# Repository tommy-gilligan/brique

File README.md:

<p align="center">
  
  <h3 align="center">Brique</h3>
  <p align="center">
    An RP2354-based replacement mainboard for Nokia 3310.<br />
    Rust firmware with browser-based simulator included. 
    <br />
    <br />
    Software: <a href="https://tommy-gilligan.github.io/brique/simulation">Simulation</a>
    ·
    <a href="https://tommy-gilligan.github.io/brique/doc/shared">API</a>
    <br />
    Hardware: <a href="https://github.com/tommy-gilligan/brique/releases/latest/download/gerbers.zip">Gerbers</a>
    ·
    <a href="https://github.com/tommy-gilligan/brique/releases/latest/download/bom.csv">BOM</a>
    ·
    <a href="https://github.com/tommy-gilligan/brique/releases/latest/download/cpl.csv">CPL</a>
    ·
    <a href="https://github.com/tommy-gilligan/brique/releases/latest/download/schematic.pdf">Schematic</a>
    ·
    <a href="https://github.com/tommy-gilligan/brique/releases/latest/download/pcb.svg">PCB Layout</a>
  </p>
</p>
<hr/>
This started as a cute "what if?":

> What if I could type out messages on my smart phone by using tactile buttons like I used to have on my phone back in high school?

Because the board would need to fit into the chassis of a Nokia 3310 and because there are existing doodads that would be sitting alongside the board anyways, scope has crept to include connecting to these other thingamajigs.

## Assuming Rustup
```
curl --proto '=https' --tlsv1.2 -sSf https://sh.rustup.rs | sh
```
- select nightly
- load into shell

## Setting up web environment

```
cargo install --locked trunk
cd web
trunk serve
```

## Setting up rp environment

- Setting up board
    - Install Hardware Test Program
    - Reassemble 3310
    - Manual Test

## Ordering from JLCPCB
1.  Download the following files from [the latest release](https://github.com/tommy-gilligan/brique/releases/latest):
    - [gerbers.zip](https://github.com/tommy-gilligan/brique/releases/latest/download/gerbers.zip)
    - [bom.csv](https://github.com/tommy-gilligan/brique/releases/latest/download/bom.csv)
    - [cpl.csv](https://github.com/tommy-gilligan/brique/releases/latest/download/cpl.csv)
2. Upload `gerbers.zip`
3. Set `PCB Thickness` to `1.0mm`.  This is the thickness of the original board that is being replaced.  The case is not designed for boards that are not 1mm thick.
4. Enable `PCB Assembly`
5. Set `Assembly Side` to `Bottom Side`
6. Set `PCBA Qty` to `2` (or however many you like, but 2 is the minimum)
7. Click `Next` to be taken to the next page
8. Upload `bom.csv`
9. Upload `cpl.csv`
10. Click `Process BOM & CPL`

### TODO

- document app API

- give more control over display flushing, keep track of what needs updating, what needs flushing
	- display can do 90deg rotated addressing
- allow setting time
- rp2350 very low power state
- make all system work live on primary core.  give apps dedicated secondary core.
- 'pre-emption'
- priveledged, background blocking system calls  
- defmt should be used if possible (instead of log).  currently it is used for uart/rtt but for usb i'm using log.  is there a way to use usb logging from defmt?  will probably require a bit of a bit deep dive
- placement of some parts is off (rotation for U*)
- switch off after 5 minutes idle (switching on takes no time)
- power button: can this be triggered by 'any key'?  ie. any keypad press turns the device on.  there's enough GPIO to spare that we should have a dedicated GPIO for any key too)
- power button should turn on device but also function as gpio?

https://serdisplib.sourceforge.net/ser/pcd8544.html

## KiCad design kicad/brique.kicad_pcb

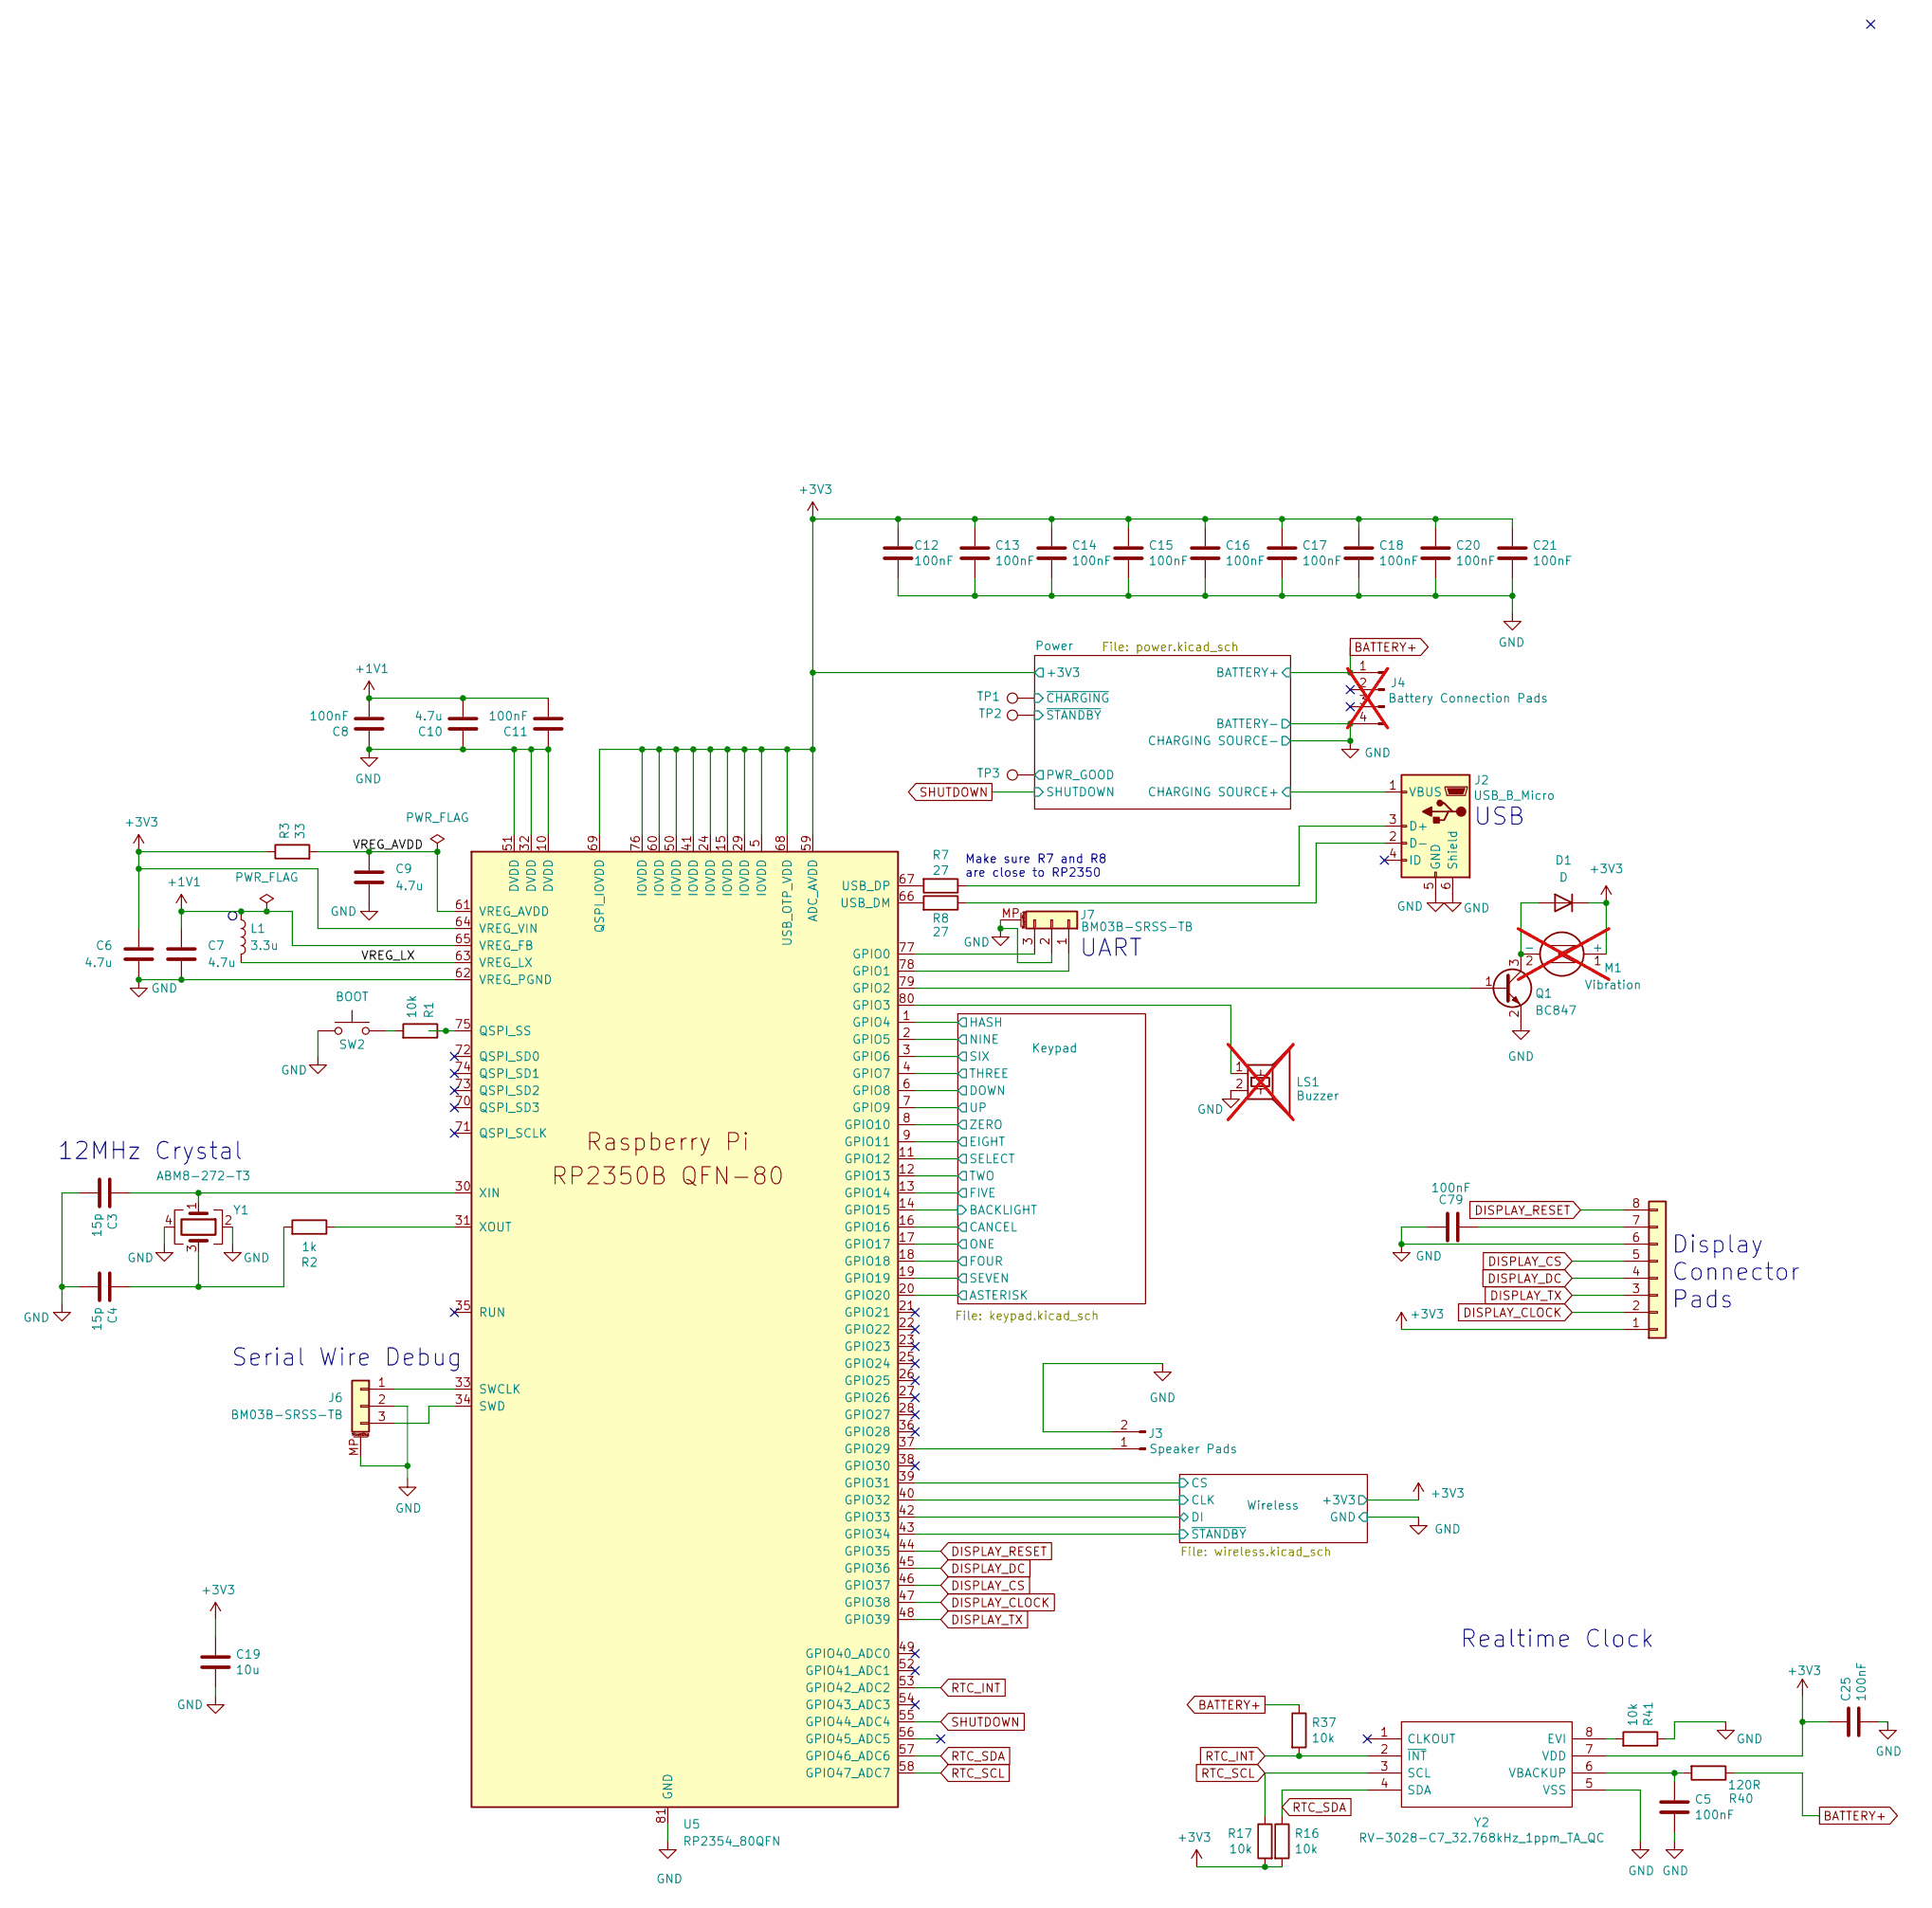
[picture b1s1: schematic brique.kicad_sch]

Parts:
C3, C4: 15p; C_0402_1005Metric; JLCPCB C86285
C5, C8, C11, C12, C13, C14, C15, C16, C17, C18, C20, C21, C79: 100nF; C_0402_1005Metric; JLCPCB C1525
C6, C7, C9, C10: 4.7u; C_0402_1005Metric; JLCPCB C368809
C19: 10u; C_0805_2012Metric; JLCPCB C17024
C25: 100nF; C_0805_2012Metric; JLCPCB C49678
D1: D; D_0402_1005Metric; JLCPCB C2837790
J1: Conn_01x07; screen
J2: USB_B_Micro; USB_Micro-B_Molex_47346-0001; JLCPCB C132560
J3: Speaker Pads; PinHeader_1x02_P1.00mm_Vertical_SMD_Pin1Left
J4: Battery Connection Pads; battery; not fitted
J6, J7: BM03B-SRSS-TB; JST_SH_SM03B-SRSS-TB_1x03-1MP_P1.00mm_Horizontal; JLCPCB C160389
L1: 3.3u; L_pol_2016; JLCPCB C42411119
LS1: Buzzer; buzzer; not fitted
M1: Vibration; vibrator; not fitted
Q1: BC847; SOT-23; JLCPCB C391423
R1, R16, R17, R37, R41: 10k; R_0402_1005Metric; JLCPCB C60490
R2: 1k; R_0402_1005Metric; JLCPCB C25543
R3: 33; R_0402_1005Metric; JLCPCB C852729
R7, R8: 27; R_0402_1005Metric; JLCPCB C25100
R40: 120R; R_0402_1005Metric; JLCPCB C114758
SW2: BOOT; SW_SPST_PTS810; JLCPCB C221895
TP1, TP2, TP3: TestPoint; TestPoint_THTPad_D1.5mm_Drill0.7mm
U5: RP2354_80QFN; RP2350-QFN-80-1EP_10x10_P0.4mm_EP3.4x3.4mm_ThermalVias; JLCPCB C39843328
Y1: ABM8-272-T3; Crystal_SMD_3225-4Pin_3.2x2.5mm; JLCPCB C20625731
Y2: RV-3028-C7_32.768kHz_1ppm_TA_QC; MicroCrystal_RV3028C7; Mouser Part Number 428-203591-MG01

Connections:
+1V1: C7.1, C8.2, C10.2, C11.2, L1.1, U5.65 (VREG_FB)
+3V3: C6.1, C12.1, C13.1, C14.1, C15.1, C16.1, C17.1, C18.1, C19.1, C20.1, C21.1, C25.1, D1.1 (K), J1.1, M1.1 (+), R3.1, R16.2, R17.2, U5.5 (IOVDD), U5.15 (IOVDD), U5.24 (IOVDD), U5.29 (IOVDD), U5.41 (IOVDD), U5.50 (IOVDD), U5.59 (ADC_AVDD), U5.60 (IOVDD), U5.64 (VREG_VIN), U5.68 (USB_OTP_VDD), U5.69 (QSPI_IOVDD), U5.76 (IOVDD), Y2.7 (VDD); also elsewhere on the board
/Keypad/ASTERISK: U5.20 (GPIO20); also elsewhere on the board
/Keypad/BACKLIGHT: U5.14 (GPIO15); also elsewhere on the board
/Keypad/CANCEL: U5.16 (GPIO16); also elsewhere on the board
/Keypad/DOWN: U5.6 (GPIO8); also elsewhere on the board
/Keypad/EIGHT: U5.9 (GPIO11); also elsewhere on the board
/Keypad/FIVE: U5.13 (GPIO14); also elsewhere on the board
/Keypad/FOUR: U5.18 (GPIO18); also elsewhere on the board
/Keypad/HASH: U5.1 (GPIO4); also elsewhere on the board
/Keypad/NINE: U5.2 (GPIO5); also elsewhere on the board
/Keypad/ONE: U5.17 (GPIO17); also elsewhere on the board
/Keypad/SELECT: U5.11 (GPIO12); also elsewhere on the board
/Keypad/SEVEN: U5.19 (GPIO19); also elsewhere on the board
/Keypad/SIX: U5.3 (GPIO6); also elsewhere on the board
/Keypad/THREE: U5.4 (GPIO7); also elsewhere on the board
/Keypad/TWO: U5.12 (GPIO13); also elsewhere on the board
/Keypad/UP: U5.7 (GPIO9); also elsewhere on the board
/Keypad/ZERO: U5.8 (GPIO10); also elsewhere on the board
/Power/CHARGING SOURCE+: J2.1 (VBUS); also elsewhere on the board
/Power/PWR_GOOD: TP3.1; also elsewhere on the board
/Power/~CHARGING: TP1.1; also elsewhere on the board
/Power/~STANDBY: TP2.1; also elsewhere on the board
/VREG_AVDD: C9.1, R3.2, U5.61 (VREG_AVDD)
/VREG_LX: L1.2, U5.63 (VREG_LX)
/Wireless/CLK: U5.40 (GPIO32); also elsewhere on the board
/Wireless/CS: U5.39 (GPIO31); also elsewhere on the board
/Wireless/DI: U5.42 (GPIO33); also elsewhere on the board
/Wireless/~STANDBY: U5.43 (GPIO34); also elsewhere on the board
BATTERY+: J4.1, R37.1, R40.1; also elsewhere on the board
DISPLAY_CLOCK: J1.2, U5.47 (GPIO38)
DISPLAY_CS: J1.5, U5.46 (GPIO37)
DISPLAY_DC: J1.4, U5.45 (GPIO36)
DISPLAY_RESET: J1.8, U5.44 (GPIO35)
DISPLAY_TX: J1.3, U5.48 (GPIO39)
GND: C3.2, C4.2, C5.2, C6.2, C7.2, C8.1, C9.2, C10.1, C11.1, C12.2, C13.2, C14.2, C15.2, C16.2, C17.2, C18.2, C19.2, C20.2, C21.2, C25.2, C79.1, J1.6, J2.5 (GND), J2.6 (Shield), J3.2, J4.4, J6.2, J6.MP (MountPin), J7.2, J7.MP (MountPin), LS1.2, Q1.2 (E), R41.1, SW2.1, U5.10 (DVDD), U5.32 (DVDD), U5.51 (DVDD), U5.62 (VREG_PGND), U5.81 (GND), Y1.2, Y1.4, Y2.5 (VSS); also elsewhere on the board
unnamed: C4.1, R2.2, Y1.3
unnamed: D1.2 (A), M1.2 (-), Q1.3 (C)
unnamed: C79.2, J1.7
unnamed: J2.3 (D+), R7.1
unnamed: J2.2 (D-), R8.1
unnamed: J3.1, U5.37 (GPIO29)
unnamed: J6.1, U5.33 (SWCLK)
unnamed: J6.3, U5.34 (SWD)
unnamed: J7.1, U5.78 (GPIO1)
unnamed: J7.3, U5.77 (GPIO0)
unnamed: Q1.1 (B), U5.79 (GPIO2)
unnamed: R1.2, SW2.2
unnamed: LS1.1, U5.80 (GPIO3)
unnamed: R1.1, U5.75 (QSPI_SS)
unnamed: R8.2, U5.66 (USB_DM)
unnamed: R7.2, U5.67 (USB_DP)
unnamed: C3.1, U5.30 (XIN), Y1.1
unnamed: R2.1, U5.31 (XOUT)
unnamed: R41.2, Y2.8 (EVI)
unnamed: C5.1, R40.2, Y2.6 (VBACKUP)
RTC_INT: R37.2, U5.53 (GPIO42_ADC2), Y2.2 (~INT)
RTC_SCL: R17.1, U5.58 (GPIO47_ADC7), Y2.3 (SCL)
RTC_SDA: R16.1, U5.57 (GPIO46_ADC6), Y2.4 (SDA)
SHUTDOWN: U5.55 (GPIO44_ADC4); also elsewhere on the board

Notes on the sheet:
Make sure R7 and R8 are close to RP2350
Serial Wire Debug
Realtime Clock
Display Connector Pads
USB
UART
12MHz Crystal

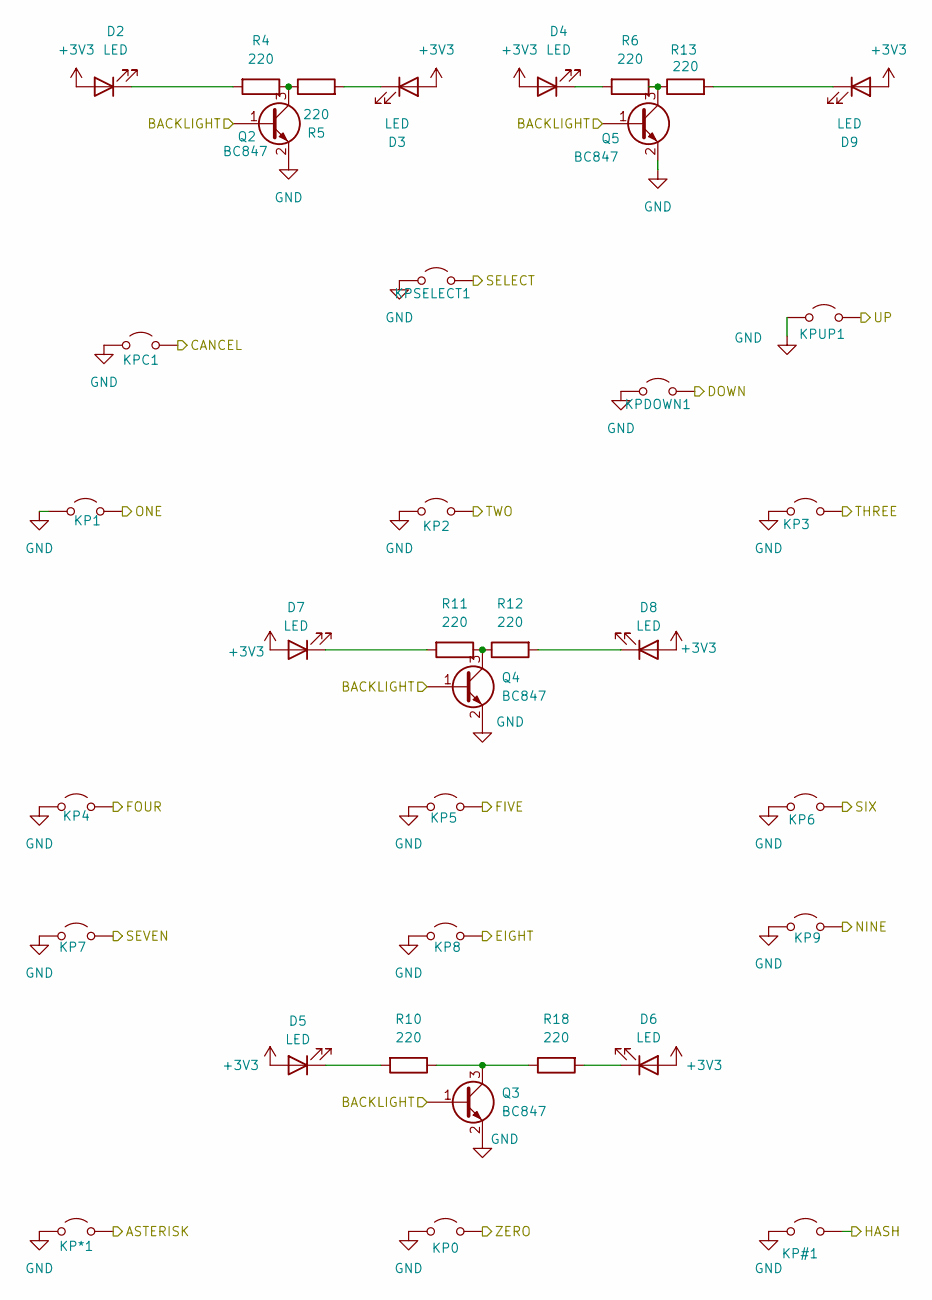
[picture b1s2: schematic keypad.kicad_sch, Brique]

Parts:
D2, D3, D4, D5, D6, D7, D8, D9: LED; LED_REVERSE; JLCPCB C3646932
KP0, KP1, KP2, KP4, KP5, KP6, KP7, KP8, KP9: Jumper_2_Open; ButtonPads
KP3: 3; ButtonPads
KP#1: Jumper_2_Open; ButtonPads
KP*1: Jumper_2_Open; ButtonPads
KPC1: C; ButtonPads
KPDOWN1: Jumper_2_Open; ButtonPads
KPSELECT1: Jumper_2_Open; ButtonPads
KPUP1: Jumper_2_Open; ButtonPads
Q2, Q3, Q4, Q5: BC847; SOT-23; JLCPCB C391423
R4, R5, R6, R10, R11, R12, R13, R18: 220; R_0402_1005Metric; JLCPCB C112291

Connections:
+3V3: D2.2 (A), D3.2 (A), D4.2 (A), D5.2 (A), D6.2 (A), D7.2 (A), D8.2 (A), D9.2 (A); also elsewhere on the board
/Keypad/ASTERISK: KP*1.2 (B); also elsewhere on the board
/Keypad/BACKLIGHT: Q2.1 (B), Q3.1 (B), Q4.1 (B), Q5.1 (B); also elsewhere on the board
/Keypad/CANCEL: KPC1.2 (B); also elsewhere on the board
/Keypad/DOWN: KPDOWN1.2 (B); also elsewhere on the board
/Keypad/EIGHT: KP8.2 (B); also elsewhere on the board
/Keypad/FIVE: KP5.2 (B); also elsewhere on the board
/Keypad/FOUR: KP4.2 (B); also elsewhere on the board
/Keypad/HASH: KP#1.2 (B); also elsewhere on the board
/Keypad/NINE: KP9.2 (B); also elsewhere on the board
/Keypad/ONE: KP1.2 (B); also elsewhere on the board
/Keypad/SELECT: KPSELECT1.2 (B); also elsewhere on the board
/Keypad/SEVEN: KP7.2 (B); also elsewhere on the board
/Keypad/SIX: KP6.2 (B); also elsewhere on the board
/Keypad/THREE: KP3.2 (B); also elsewhere on the board
/Keypad/TWO: KP2.2 (B); also elsewhere on the board
/Keypad/UP: KPUP1.2 (B); also elsewhere on the board
/Keypad/ZERO: KP0.2 (B); also elsewhere on the board
GND: KP0.1 (A), KP1.1 (A), KP2.1 (A), KP3.1 (A), KP4.1 (A), KP5.1 (A), KP6.1 (A), KP7.1 (A), KP8.1 (A), KP9.1 (A), KP#1.1 (A), KP*1.1 (A), KPC1.1 (A), KPDOWN1.1 (A), KPSELECT1.1 (A), KPUP1.1 (A), Q2.2 (E), Q3.2 (E), Q4.2 (E), Q5.2 (E); also elsewhere on the board
unnamed: D2.1 (K), R4.2
unnamed: D3.1 (K), R5.2
unnamed: D4.1 (K), R6.2
unnamed: D5.1 (K), R10.2
unnamed: D6.1 (K), R18.2
unnamed: D7.1 (K), R11.2
unnamed: D8.1 (K), R12.2
unnamed: D9.1 (K), R13.2
unnamed: Q2.3 (C), R4.1, R5.1
unnamed: Q3.3 (C), R10.1, R18.1
unnamed: Q4.3 (C), R11.1, R12.1
unnamed: Q5.3 (C), R6.1, R13.1

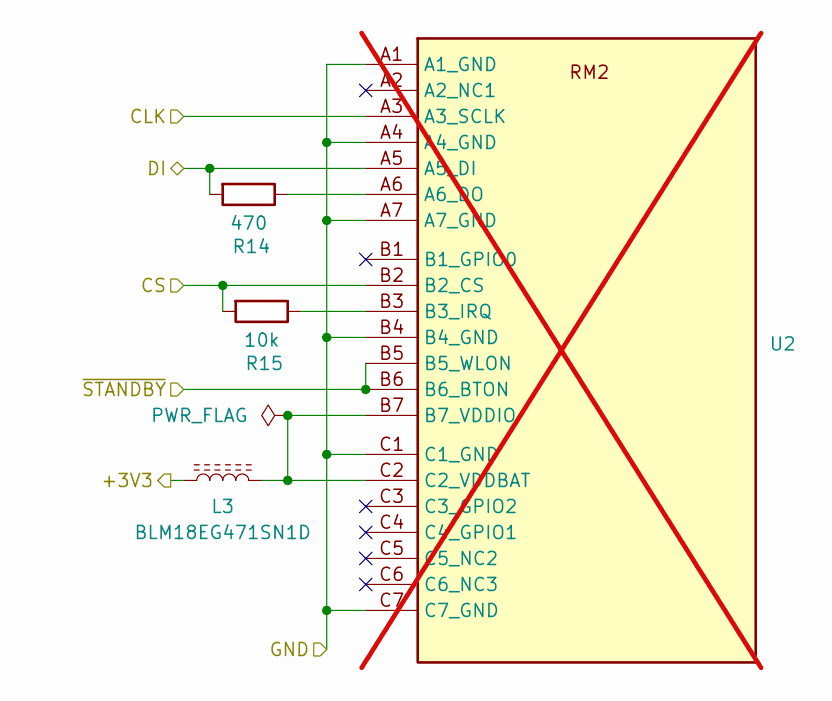
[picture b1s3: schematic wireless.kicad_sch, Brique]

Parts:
L3: BLM18EG471SN1D; L_0201_0603Metric; JLCPCB C337880
R14: 470; R_0402_1005Metric; JLCPCB C114877
R15: 10k; R_0402_1005Metric; JLCPCB C60490
U2: RM2; not fitted

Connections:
+3V3: L3.1; also elsewhere on the board
/Wireless/CLK: U2.A3 (A3_SCLK); also elsewhere on the board
/Wireless/CS: R15.2, U2.B2 (B2_CS); also elsewhere on the board
/Wireless/DI: R14.2, U2.A5 (A5_DI); also elsewhere on the board
/Wireless/~STANDBY: U2.B5 (B5_WLON), U2.B6 (B6_BTON); also elsewhere on the board
GND: U2.A1 (A1_GND), U2.A4 (A4_GND), U2.A7 (A7_GND), U2.B4 (B4_GND), U2.C1 (C1_GND), U2.C7 (C7_GND); also elsewhere on the board
unnamed: R14.1, U2.A6 (A6_DO)
unnamed: R15.1, U2.B3 (B3_IRQ)
unnamed: L3.2, U2.B7 (B7_VDDIO), U2.C2 (C2_VDDBAT)

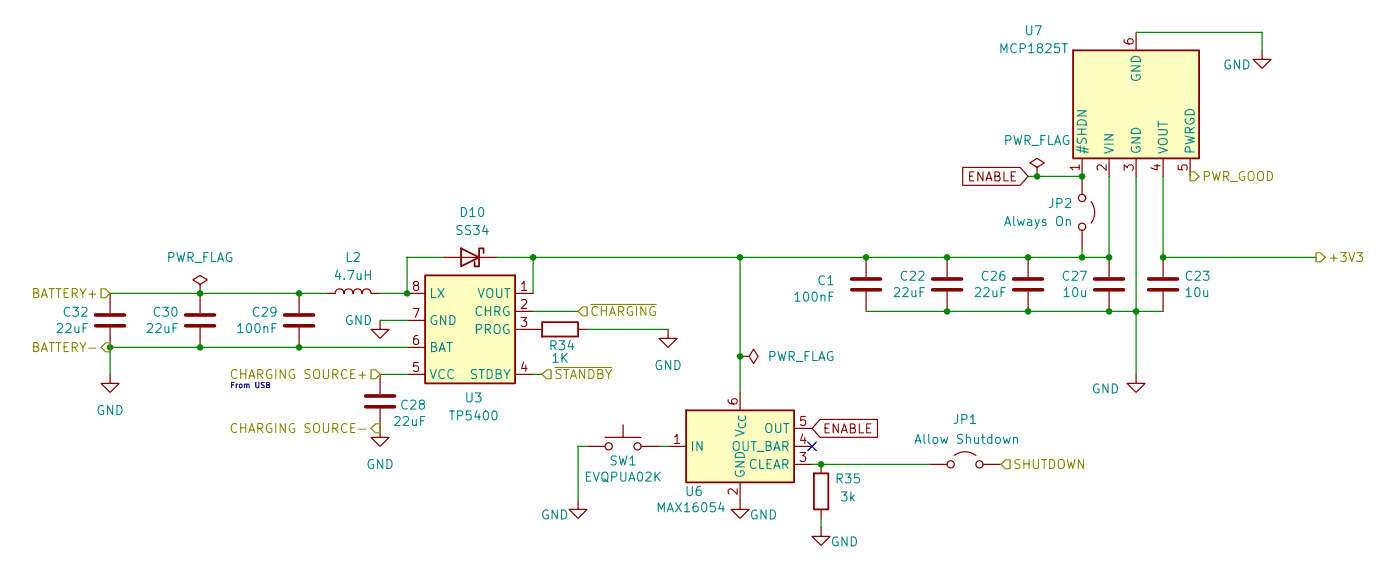
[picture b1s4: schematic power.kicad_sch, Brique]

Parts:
C1, C29: 100nF; C_0805_2012Metric; JLCPCB C49678
C22, C26, C28, C30, C32: 22uF; C_0805_2012Metric; JLCPCB C602037
C23, C27: 10u; C_0805_2012Metric; JLCPCB C17024
D10: SS34; D_SMA; JLCPCB C8678
JP1: Allow Shutdown; SolderJumper-2_P1.3mm_Open_Pad1.0x1.5mm
JP2: Always On; SolderJumper-2_P1.3mm_Open_Pad1.0x1.5mm
L2: 4.7uH; L_Neosid_MicroCoil_Ms36-L; JLCPCB C57269
R34: 1K; R_0402_1005Metric; JLCPCB C25543
R35: 3k; R_0402_1005Metric; JLCPCB C137872
SW1: EVQPUA02K; power switch; JLCPCB C128539
U3: TP5400; SOIC-8_3.9x4.9mm_P1.27mm; JLCPCB C2891434
U6: MAX16054; SOT-23-6; JLCPCB C79401
U7: MCP1825T; SOT-223-6; JLCPCB C622691

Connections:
+3V3: C23.1, U7.4 (VOUT); also elsewhere on the board
/Power/CHARGING SOURCE+: C28.1, U3.5 (VCC); also elsewhere on the board
/Power/PWR_GOOD: U7.5 (PWRGD); also elsewhere on the board
/Power/~CHARGING: U3.2 (CHRG); also elsewhere on the board
/Power/~STANDBY: U3.4 (STDBY); also elsewhere on the board
BATTERY+: C29.1, C30.1, C32.1, L2.2; also elsewhere on the board
ENABLE: JP2.2 (B), U6.5 (OUT), U7.1 (#SHDN)
GND: C1.2, C22.2, C23.2, C26.2, C27.2, C28.2, C29.2, C30.2, C32.2, R34.1, R35.1, SW1.1, U3.6 (BAT), U3.7 (GND), U6.2 (GND), U7.3 (GND), U7.6 (GND); also elsewhere on the board
unnamed: D10.2 (A), L2.1, U3.8 (LX)
unnamed: C1.1, C22.1, C26.1, C27.1, D10.1 (K), JP2.1 (A), U3.1 (VOUT), U6.6 (V_{CC}), U7.2 (VIN)
unnamed: JP1.1 (A), R35.2, U6.3 (CLEAR)
unnamed: R34.2, U3.3 (PROG)
unnamed: SW1.2, U6.1 (IN)
SHUTDOWN: JP1.2 (B); also elsewhere on the board

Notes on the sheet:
From USB

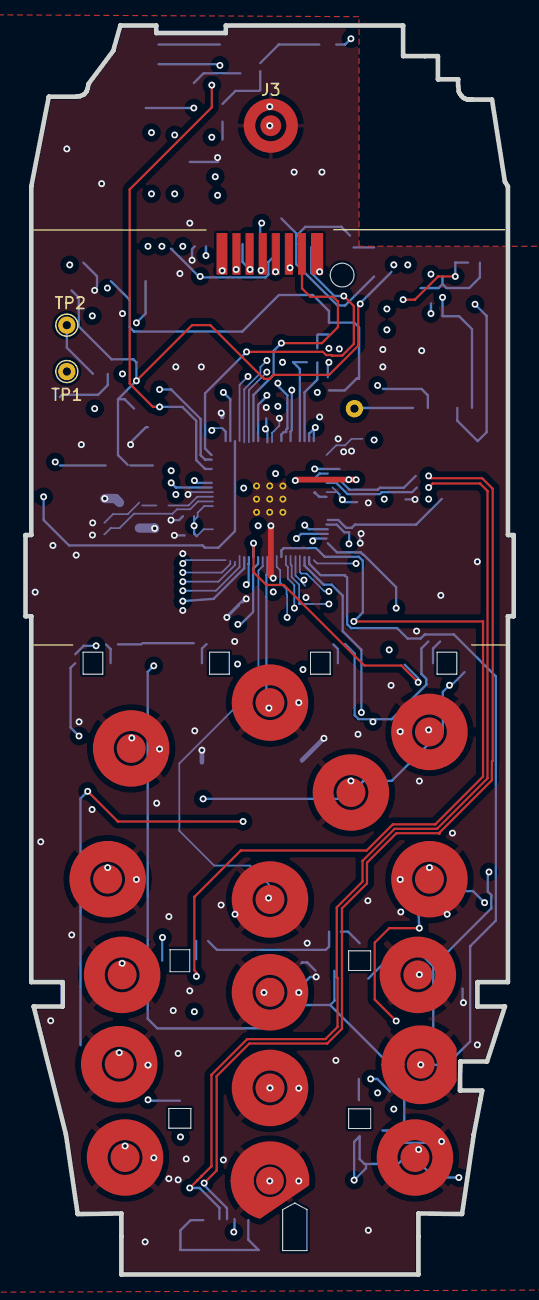
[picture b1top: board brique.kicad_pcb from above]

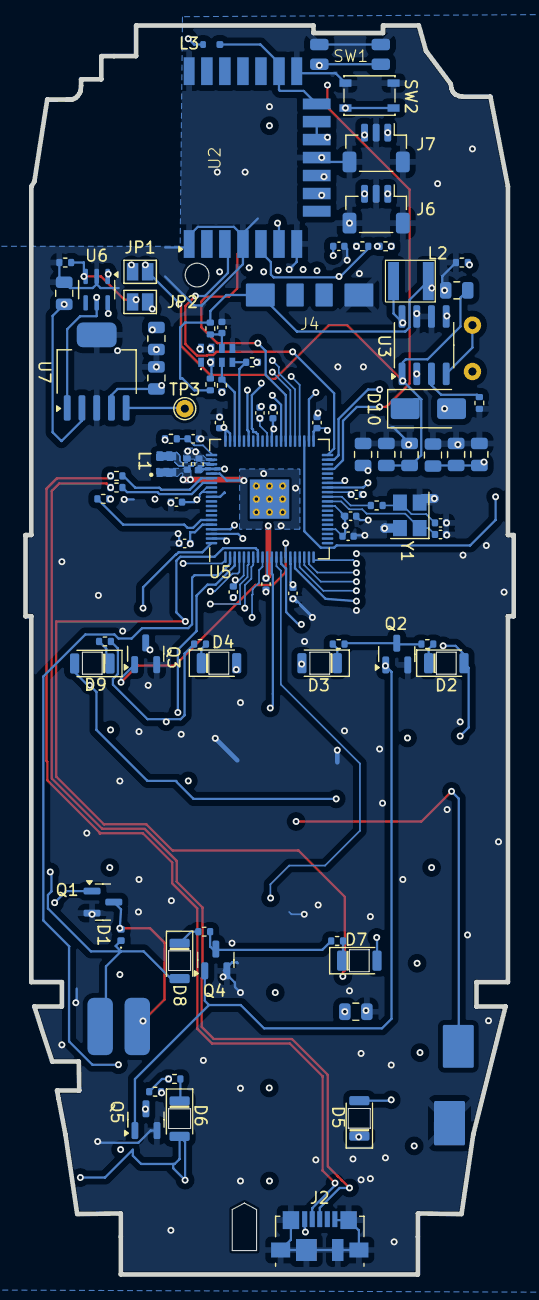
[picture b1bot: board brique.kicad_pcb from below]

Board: 4 copper layers, 42.1 x 107.7 mm, 108 parts (88 on the bottom side), 81 nets.

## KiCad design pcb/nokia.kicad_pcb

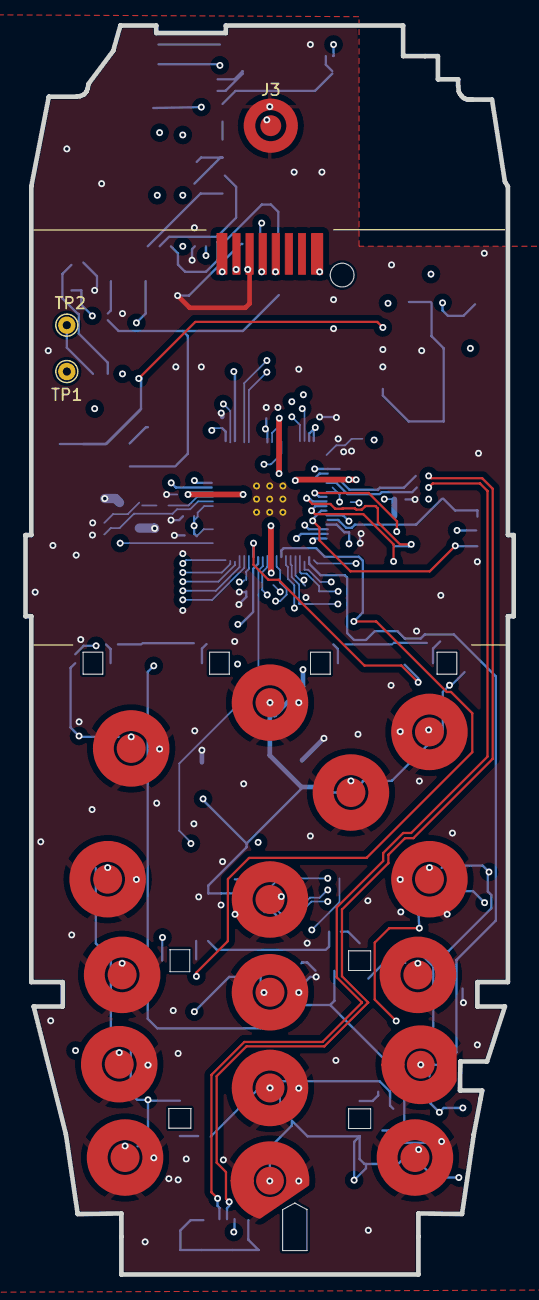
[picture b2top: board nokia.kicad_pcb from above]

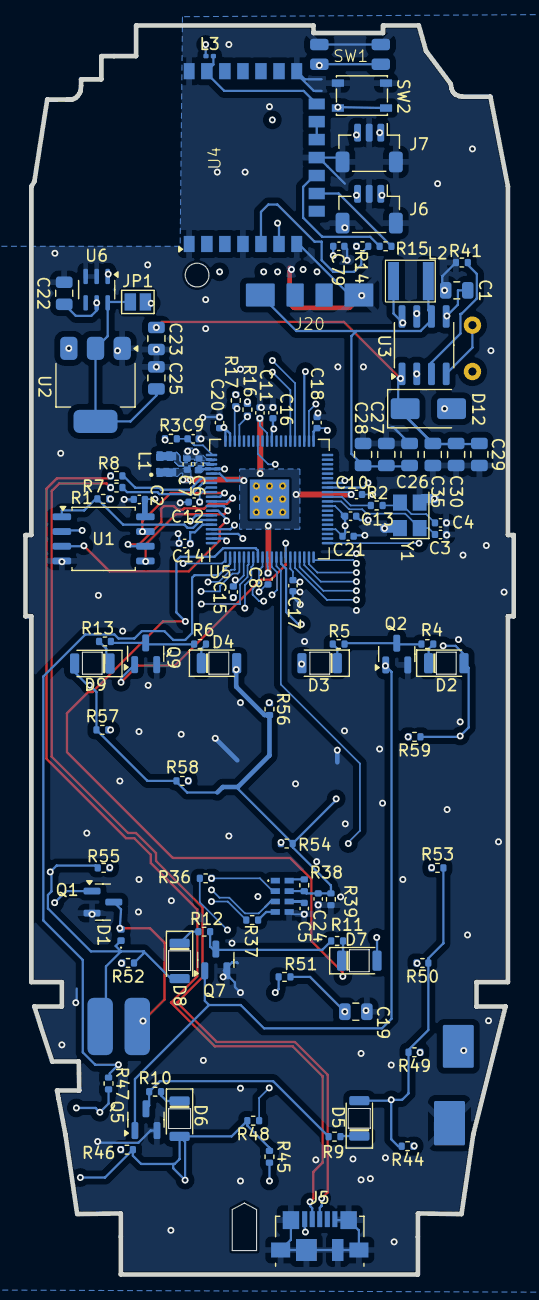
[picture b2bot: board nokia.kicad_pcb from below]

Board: 4 copper layers, 42.1 x 107.7 mm, 125 parts (105 on the bottom side), 81 nets.

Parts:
C1, C27, C28, C30, C35: 22uF; C_0805_2012Metric
C2, C5, C8, C11, C12, C13, C14, C15, C16, C17, C18, C20, C21, C24: 100n; C_0402_1005Metric
C3, C4: 15p; C_0402_1005Metric
C6, C7, C9, C10: 4.7u; C_0402_1005Metric
C19, C22, C23, C25: 10u; C_0805_2012Metric
C26, C29: 100nF; C_0805_2012Metric
C79: 100nF; C_0402_1005Metric
D1: D; D_0402_1005Metric
D2, D3, D4, D5, D6, D7, D8, D9: LED; LED_REVERSE
D12: SS34; D_SMA
J1: Conn_01x07; screen
J3: Conn_01x02_Pin; PinHeader_1x02_P1.00mm_Vertical_SMD_Pin1Left
J5: USB_B_Micro; USB_Micro-B_Molex_47346-0001
J6, J7: SM03B-SRSS-TB; JST_SH_BM03B-SRSS-TB_1x03-1MP_P1.00mm_Vertical
J20: Battery Connection Pads; battery
JP1: Jumper_2_Open; SolderJumper-2_P1.3mm_Open_Pad1.0x1.5mm
KP0, KP1, KP2, KP4, KP5, KP6, KP7, KP8, KP9: Jumper_2_Open; thick-pad
KP3: 3; thick-pad
KP#1: Jumper_2_Open; thick-pad
KP*1: Jumper_2_Open; thick-pad
KPC1: C; thick-pad
KPDOWN1: Jumper_2_Open; thick-pad
KPSELECT1: Jumper_2_Open; thick-pad
KPUP1: Jumper_2_Open; thick-pad
L1: 3.3u; L_pol_2016
L2: 4.7uH; L_Neosid_MicroCoil_Ms36-L
L3: BLM18EG471SN1D; L_0201_0603Metric
LS2: Buzzer; buzzer
M1: Vibration; vibrator
Q1, Q2, Q5, Q7, Q9: BC847; SOT-23
R1, R15, R16, R17, R36, R38: 10k; R_0402_1005Metric
R2: 1k; R_0402_1005Metric
R3: 33; R_0402_1005Metric
R4, R5, R6, R9, R10, R11, R12, R13: 220; R_0402_1005Metric
R7, R8: 27; R_0402_1005Metric
R14: 470; R_0402_1005Metric
R37: 120R; R_0402_1005Metric
R39: 100k; R_0402_1005Metric
R41: 1K; R_0402_1005Metric
R44, R45, R46, R47, R48, R49, R50, R51, R52, R53, R54, R55, R56, R57, R58, R59: 3k; R_0402_1005Metric
SW1: SW_Push; power switch
SW2: SW_Push; SW_SPST_PTS810
TP1, TP2: TestPoint; TestPoint_THTPad_D1.5mm_Drill0.7mm
U1: W25Q128JVS; SOIC-8_5.23x5.23mm_P1.27mm
U2: NCP1117-3.3_SOT223; SOT-223-3_TabPin2
U3: TP5400; SOIC-8_3.9x4.9mm_P1.27mm
U4: RM2
U5: RP2350_80QFN; RP2350-QFN-80-1EP_10x10_P0.4mm_EP3.4x3.4mm_ThermalVias
U6: MAX16054; SOT-23-6
Y1: ABM8-272-T3; Crystal_SMD_3225-4Pin_3.2x2.5mm
Y2: RV-3028-C7_32.768kHz_1ppm_TA_QC; MicroCrystal_RV3028C7

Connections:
+1V1: C7.1, C8.1, C10.1, C11.1, L1.1, U5.10 (DVDD), U5.32 (DVDD), U5.51 (DVDD), U5.65 (VREG_FB)
+3V3: C2.1, C6.1, C12.1, C13.1, C14.1, C15.1, C16.1, C17.1, C18.1, C19.1, C20.1, C21.1, C22.1, C24.1, D1.1 (K), D2.2 (A), D3.2 (A), D4.2 (A), D5.2 (A), D6.2 (A), D7.2 (A), D8.2 (A), D9.2 (A), J1.1, JP1.2 (B), L3.1, M1.1 (+), R3.1, R16.2, R17.1, R36.1, R38.1, R39.1, R44.2, R45.2, R46.2, R47.2, R48.2, R49.2, R50.1, R51.1, R52.1, R53.2, R54.2, R55.1, R56.2, R57.1, R58.1, R59.1, U1.8 (VCC), U5.5 (IOVDD), U5.15 (IOVDD), U5.24 (IOVDD), U5.29 (IOVDD), U5.41 (IOVDD), U5.50 (IOVDD), U5.59 (ADC_AVDD), U5.60 (IOVDD), U5.64 (VREG_VIN), U5.68 (USB_OTP_VDD), U5.69 (QSPI_IOVDD), U5.76 (IOVDD), U6.5 (OUT), Y2.7 (VDD)
+5V: C23.1, C29.2, C30.2, C35.2, D12.1 (K), U2.3 (VI), U3.1 (VOUT)
+BATT: C26.1, C27.1, C28.1, J20.1, L2.2, U3.6 (BAT)
-BATT: C1.2, C2.2, C3.2, C4.2, C5.2, C6.2, C7.2, C8.2, C9.2, C10.2, C11.2, C12.2, C13.2, C14.2, C15.2, C16.2, C17.2, C18.2, C19.2, C20.2, C21.2, C22.2, C23.2, C24.2, C25.2, C26.2, C27.2, C28.2, C29.1, C30.1, C35.1, C79.1, J1.6, J3.2, J5.5 (GND), J5.6 (Shield), J6.2, J6.MP (MountPin), J7.2, J7.MP (MountPin), J20.4, KP0.1 (A), KP1.1 (A), KP2.1 (A), KP3.1 (A), KP4.1 (A), KP5.1 (A), KP6.1 (A), KP7.1 (A), KP8.1 (A), KP9.1 (A), KP#1.1 (A), KP*1.1 (A), KPC1.1 (A), KPDOWN1.1 (A), KPSELECT1.1 (A), KPUP1.1 (A), LS2.2, Q1.2 (E), Q2.2 (E), Q5.2 (E), Q7.2 (E), Q9.2 (E), R39.2, R41.1, SW1.1, SW2.1, U1.4 (GND), U2.1 (GND), U3.7 (GND), U4.A1 (A1_GND), U4.A4 (A4_GND), U4.A7 (A7_GND), U4.B4 (B4_GND), U4.C1 (C1_GND), U4.C7 (C7_GND), U5.62 (VREG_PGND), U5.81 (GND), U6.2 (GND), U6.3 (CLEAR), Y1.2, Y1.4, Y2.5 (VSS)
/VREG_AVDD: C9.1, R3.2, U5.61 (VREG_AVDD)
/VREG_LX: L1.2, U5.63 (VREG_LX)
EVI: R38.2, Y2.8 (EVI)
GPIO0: J7.3, U5.77 (GPIO0)
GPIO1: J7.1, U5.78 (GPIO1)
GPIO2: Q1.1 (B), U5.79 (GPIO2)
GPIO4: KP#1.2 (B), R46.1, U5.1 (GPIO4)
GPIO5: KP9.2 (B), R47.1, U5.2 (GPIO5)
GPIO6: KP6.2 (B), R52.2, U5.3 (GPIO6)
GPIO7: KP3.2 (B), R55.2, U5.4 (GPIO7)
GPIO8: KPDOWN1.2 (B), R58.2, U5.6 (GPIO8)
GPIO9: KPUP1.2 (B), R57.2, U5.7 (GPIO9)
GPIO10: KP0.2 (B), R45.1, U5.8 (GPIO10)
GPIO11: KP8.2 (B), R48.1, U5.9 (GPIO11)
GPIO12: KPSELECT1.2 (B), R56.1, U5.11 (GPIO12)
GPIO13: KP2.2 (B), R54.1, U5.12 (GPIO13)
GPIO14: KP5.2 (B), R51.2, U5.13 (GPIO14)
GPIO15: Q2.1 (B), Q5.1 (B), Q7.1 (B), Q9.1 (B), U5.14 (GPIO15)
GPIO16: KPC1.2 (B), R59.2, U5.16 (GPIO16)
GPIO17: KP1.2 (B), R53.1, U5.17 (GPIO17)
GPIO18: KP4.2 (B), R50.2, U5.18 (GPIO18)
GPIO19: KP7.2 (B), R49.1, U5.19 (GPIO19)
GPIO20: KP*1.2 (B), R44.1, U5.20 (GPIO20)
GPIO21: LS2.1, U5.21 (GPIO21)
GPIO33: J1.8, U5.42 (GPIO33)
GPIO34: J3.1, U5.43 (GPIO34)
GPIO36: J1.4, U5.45 (GPIO36)
GPIO37: J1.5, U5.46 (GPIO37)
unnamed: C4.1, R2.2, Y1.3
unnamed: D1.2 (A), M1.2 (-), Q1.3 (C)
unnamed: D2.1 (K), R4.2
unnamed: D3.1 (K), R5.2
unnamed: D4.1 (K), R6.2
unnamed: D5.1 (K), R9.2
unnamed: D6.1 (K), R10.2
unnamed: D7.1 (K), R11.2
unnamed: D8.1 (K), R12.2
unnamed: D9.1 (K), R13.2
unnamed: D12.2 (A), L2.1, U3.8 (LX)
unnamed: C79.2, J1.7
unnamed: C25.1, JP1.1 (A), U2.2 (VO), U6.6 (V_{CC})
unnamed: Q2.3 (C), R4.1, R5.1
unnamed: Q5.3 (C), R9.1, R10.1
unnamed: Q7.3 (C), R11.1, R12.1
unnamed: Q9.3 (C), R6.1, R13.1
unnamed: R1.2, SW2.2
unnamed: TP1.1, U3.2 (CHRG)
unnamed: R41.2, U3.3 (PROG)
unnamed: TP2.1, U3.4 (STDBY)
unnamed: R14.1, U4.A6 (A6_DO)
unnamed: R15.1, U4.B3 (B3_IRQ)
unnamed: L3.2, U4.B7 (B7_VDDIO), U4.C2 (C2_VDDBAT)
unnamed: R8.2, U5.66 (USB_DM)
unnamed: R7.2, U5.67 (USB_DP)
unnamed: SW1.2, U6.1 (IN)
unnamed: R37.1, Y2.4 (SDA)
unnamed: C5.1, Y2.6 (VBACKUP)
QSPI_SCLK: U1.6 (CLK), U5.71 (QSPI_SCLK)
QSPI_SD0: U1.5 (DI(IO0)), U5.72 (QSPI_SD0)
QSPI_SD1: U1.2 (DO(IO1)), U5.74 (QSPI_SD1)
QSPI_SD2: U1.3 (IO2), U5.73 (QSPI_SD2)
QSPI_SD3: U1.7 (IO3), U5.70 (QSPI_SD3)
QSPI_SS: R1.1, U1.1 (~CS), U5.75 (QSPI_SS)
RM2_CS: R15.2, U4.B2 (B2_CS)
RM2_DIO: R14.2, U4.A5 (A5_DI)
RM2_POWER: U4.B5 (B5_WLON), U4.B6 (B6_BTON)
RTC_SCL: R17.2, U5.58 (GPIO47_ADC7), Y2.3 (SCL)
RTC_SDA: R16.1, R37.2, U5.57 (GPIO46_ADC6)
SWCLK: J6.1, U5.33 (SWCLK)
SWD: J6.3, U5.34 (SWD)
USB_D+: J5.3 (D+), R7.1
USB_D-: J5.2 (D-), R8.1
VBUS: C1.1, J5.1 (VBUS), U3.5 (VCC)
XIN: C3.1, U5.30 (XIN), Y1.1
XOUT: R2.1, U5.31 (XOUT)
~INT: R36.2, U5.53 (GPIO42_ADC2), Y2.2 (~INT)

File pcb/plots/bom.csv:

Comment,Designator,Footprint,JLCPCB Part #,,
SW_Push,SW1,power switch,C128539,,
10u,"C23,C25,C19",C_0805_2012Metric,C17024,,
ABM8-272-T3,Y1,Crystal_SMD_3225-4Pin_3.2x2.5mm,C20625731,,
27,"R7,R8",R_0402_1005Metric,C25100,,
1k,R2,R_0402_1005Metric,C25543,,
1K,R41,R_0402_1005Metric,C25543,,
NCP1117-3.3_SOT223,U2,SOT-223-3_TabPin2,C26537,,
D,D1,D_0402_1005Metric,C2837790,,
RV-3028-C7_32.768kHz_1ppm_TA_QC,Y2,MicroCrystal_RV3028C7,C3019759,,
4.7u,"C9,C6,C7,C10",C_0402_1005Metric,C368809,,
BC847,"Q2,Q7,Q5,Q1,Q9",SOT-23,C391423,,
3.3u,L1,L_pol_2016,C42411119,,
RP2350_80QFN,U5,RP2350-QFN-80-1EP_10x10_P0.4mm_EP3.4x3.4mm_ThermalVias,C42415655,,
10k,"R35,R34,R38,R1,R36",R_0402_1005Metric,C60490,,
100k,R39,R_0402_1005Metric,C60491,,
100n,"C12,C18,C11,C16,C5,C14,C2,C21,C17,C24,C13,C20,C15,C8",C_0402_1005Metric,C77020,,
33,R3,R_0402_1005Metric,C852729,,
15p,"C4,C3",C_0402_1005Metric,C86285,,
W25Q128JVS,U1,SOIC-8_5.23x5.23mm_P1.27mm,C97521,,
4.7uH,L2,L_Neosid_MicroCoil_Ms36-L,C48427,,
LED,"D2,D3,D4,D7,D9,D5,D6,D8",LED_REVERSE,C3646932,,
100nF,"C26,C29",C_0805_2012Metric,C1711,,
3k,"R14,R44,R54,R52,R45,R58,R51,R46,R50,R53,R47,R56,R57,R55,R59,R49,R48",R_0402_1005Metric,C137872,,
22uF,"C27,C30,C35,C1,C28",C_0805_2012Metric,C602037,,
MAX16054,U4,SOT-23-6,C79401,,
220,"R10,R9,R4,R6,R5,R13,R11,R12",R_0402_1005Metric,C137872,,
SW_Push,SW2,SW_SPST_PTS810,C221895,,
100nF,C79,C_0402_1005Metric,C77020,,
USB_B_Micro,J5,USB_Micro-B_Molex_47346-0001, C132560,,
120R,R37,R_0402_1005Metric,C114758,,
SS34,D12,D_SMA,C8678,,
TP5400,U3,SOIC-8_3.9x4.9mm_P1.27mm,C2891434,,

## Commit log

2025-03-03 add reset to boot
2025-03-09 hardware tests
2025-03-11 multitap
2025-03-12 add lock screen
2025-03-12 lint/format
2025-03-12 refactor
2025-03-13 add button up
2025-03-14 numbers
2025-03-14 held key
2025-03-14 grid menu
2025-03-15 cdc test
2025-03-17 hid, main_menu, clippy
2025-03-17 snake
2025-03-17 errors, main menu
2025-03-18 buzzer
2025-03-19 pcb v0.3
2025-03-22 fixes
2025-03-23 clock
2025-03-24 stuff
2025-03-25 prune
2025-03-25 test
2025-03-31 v0.4
2025-04-08 remove main menu
2025-04-17 snake, fix pcb errors, update menu
2025-04-18 redo menu, strip sysreq, finish ringtones closes #5
2025-04-18 add more 'apps' to CI
2025-04-22 use generic menu for grid
2025-04-29 Update embassy, fill out textbox
2025-04-29 Fix part numbers
2025-04-29 Add more directories to CI
2025-04-29 Clean up shared a bit
2025-05-02 Fix up rp, start on README instructions
2025-05-19 talk
2025-07-20 freecad test
2025-07-27 Generate stl, png, gcode from FreeCAD part
2025-07-27 update connection plate
2025-08-03 fix bad footprints
2025-08-03 update do not populate, jlcpcb instructions
2025-08-03 replace standard pcba part with economic
2025-08-03 fix bom
2025-08-03 update c25 to prevent bom aggregation
2025-08-03 remove flash
2025-08-05 remove pull ups
2025-08-05 update pcb
2025-08-05 update some references for new unavailable chip
2025-09-01 fill in JLCPCB part number
2025-09-01 fix url
2025-09-01 experiment with pov
2026-02-20 Bump keccak from 0.1.5 to 0.1.6
    Bumps [keccak](https://github.com/RustCrypto/sponges) from 0.1.5 to 0.1.6.
    - [Commits](https://github.com/RustCrypto/sponges/compare/keccak-v0.1.5...keccak-v0.1.6)
    ---
    updated-dependencies:
    - dependency-name: keccak
    dependency-version: 0.1.6
